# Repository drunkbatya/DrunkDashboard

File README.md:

# DrunkDashboard

## About

An STM32-based automotive dashboard with a sunlight-readable pixel display, running a port of the [Flipper Zero OS](https://github.com/flipperdevices/flipperzero-firmware).

### Front
<picture>
    
</picture>

### Back
<picture>
    
</picture>

### Specs
- MCU: stm32u585
- Display: Winstar WG24064, RA6963-based
- Canbus
- 8xADC
- 8x12v logic level inputs

## Hardware
Kicad source and production files lives in [hardware](./hardware) directory.

## Building
### Tools
arm-none-eabi-gcc toolchain needs to be installed, also make, python3 and icon converter deps:
```bash
python3 -m pip install -r scripts/requirements.txt 
```
openocd is required for flashing and arm-none-eabi-gdb for debugging

### Build
```bash
git submodule update --init --recursive
make
```

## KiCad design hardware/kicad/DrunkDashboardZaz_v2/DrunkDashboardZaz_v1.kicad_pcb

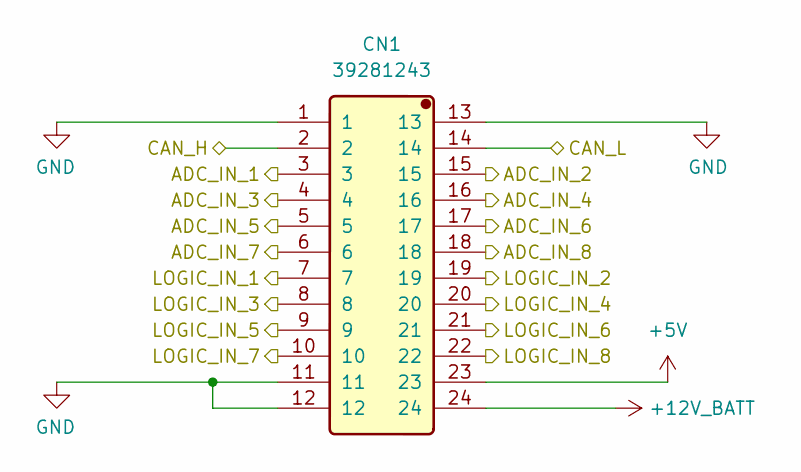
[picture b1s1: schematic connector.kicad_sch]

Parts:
CN1: 39281243; Manufacturer Part 39281243; LCSC C114088

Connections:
+5V: CN1.23; also elsewhere on the board
+12V_BATT: CN1.24; also elsewhere on the board
/ADC/ADC_IN_1: CN1.3; also elsewhere on the board
/ADC/ADC_IN_2: CN1.15; also elsewhere on the board
/ADC/ADC_IN_3: CN1.4; also elsewhere on the board
/ADC/ADC_IN_4: CN1.16; also elsewhere on the board
/ADC/ADC_IN_5: CN1.5; also elsewhere on the board
/ADC/ADC_IN_6: CN1.17; also elsewhere on the board
/ADC/ADC_IN_7: CN1.6; also elsewhere on the board
/ADC/ADC_IN_8: CN1.18; also elsewhere on the board
/CAN/CAN_H: CN1.2; also elsewhere on the board
/CAN/CAN_L: CN1.14; also elsewhere on the board
/Connector/LOGIC_IN_1: CN1.7; also elsewhere on the board
/Connector/LOGIC_IN_2: CN1.19; also elsewhere on the board
/Connector/LOGIC_IN_3: CN1.8; also elsewhere on the board
/Connector/LOGIC_IN_4: CN1.20; also elsewhere on the board
/Connector/LOGIC_IN_5: CN1.9; also elsewhere on the board
/Connector/LOGIC_IN_6: CN1.21; also elsewhere on the board
/Connector/LOGIC_IN_7: CN1.10; also elsewhere on the board
/Connector/LOGIC_IN_8: CN1.22; also elsewhere on the board
GND: CN1.1, CN1.11, CN1.12, CN1.13; also elsewhere on the board

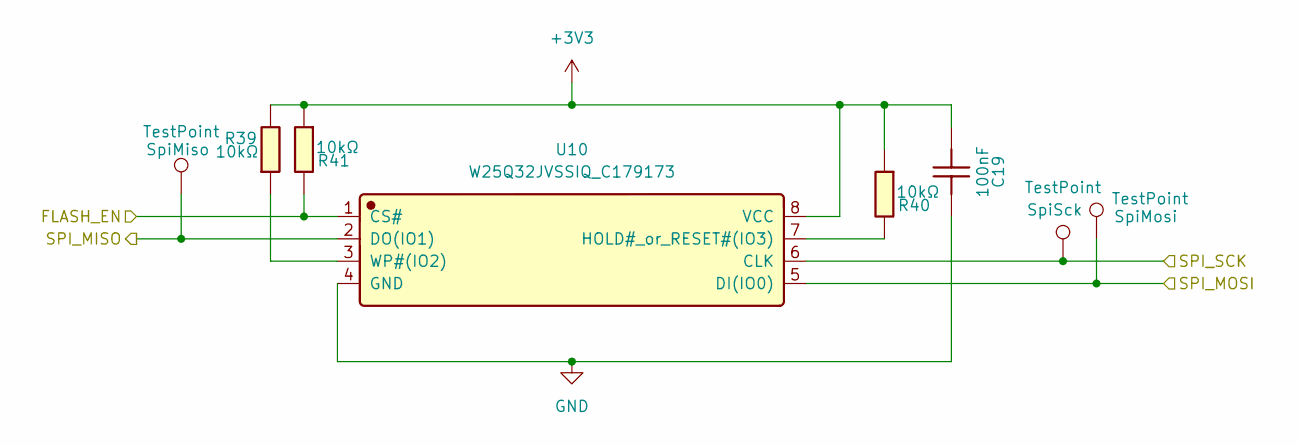
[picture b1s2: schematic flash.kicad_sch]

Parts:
C19: CL10B104KB8NNNC; C_0603_1608Metric; Manufacturer Part CL10B104KB8NNNC; LCSC C1591
R39, R40, R41: RT0603BRD0710KL; R_0603_1608Metric; Manufacturer Part RT0603BRD0710KL; LCSC C95204
SpiMiso_1: SpiMiso; TestPoint_Pad_D1.5mm
SpiMosi_1: SpiMosi; TestPoint_Pad_D1.5mm
SpiSck_1: SpiSck; TestPoint_Pad_D1.5mm
U10: W25Q32JVSSIQ_C179173; Manufacturer Part W25Q32JVSSIQ; LCSC C179173

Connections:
+3V3: C19.1, R39.2, R40.1, R41.1, U10.8 (VCC); also elsewhere on the board
/Flash/FLASH_EN: R41.2, U10.1 (CS#); also elsewhere on the board
/Flash/SPI_MISO: SpiMiso_1.1 (1_1), U10.2 (DO(IO1)); also elsewhere on the board
/Flash/SPI_MOSI: SpiMosi_1.1 (1_1), U10.5 (DI(IO0)); also elsewhere on the board
/Flash/SPI_SCK: SpiSck_1.1 (1_1), U10.6 (CLK); also elsewhere on the board
GND: C19.2, U10.4 (GND); also elsewhere on the board
unnamed: R40.2, U10.7 (HOLD#_or_RESET#(IO3))
unnamed: R39.1, U10.3 (WP#(IO2))

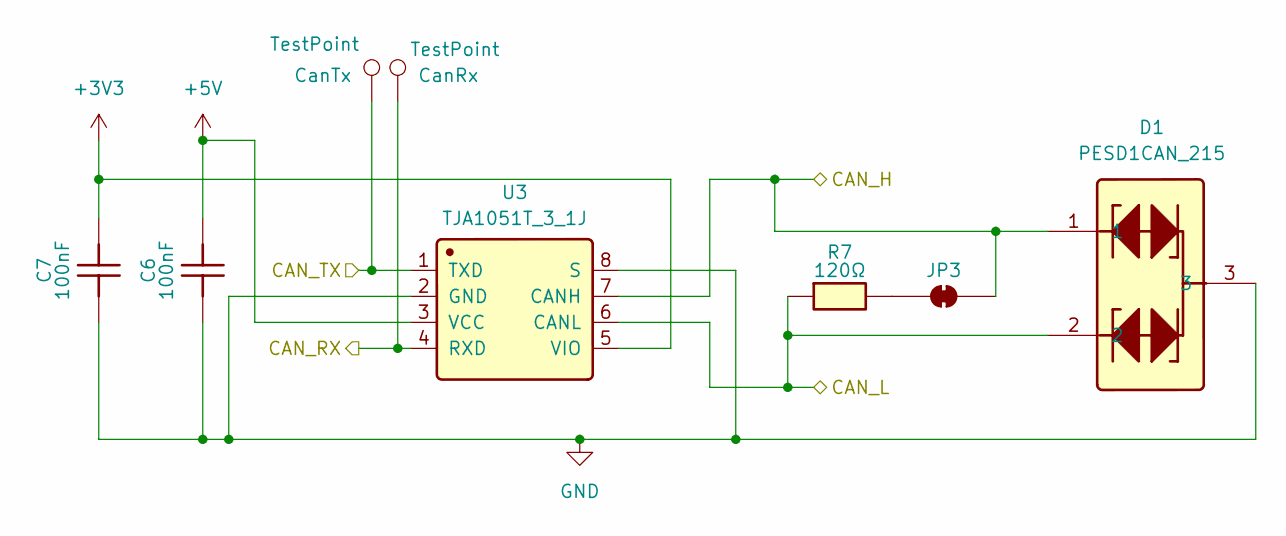
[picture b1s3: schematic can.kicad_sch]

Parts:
C6, C7: CL10B104KB8NNNC; C_0603_1608Metric; Manufacturer Part CL10B104KB8NNNC; LCSC C1591
CanRx_1: CanRx; TestPoint_Pad_D1.5mm
CanTx_1: CanTx; TestPoint_Pad_D1.5mm
D1: PESD1CAN_215; Manufacturer Part PESD1CAN,215; LCSC C15771
JP3: SolderJumper_2_Bridged; SolderJumper-2_P1.3mm_Bridged_RoundedPad1.0x1.5mm
R7: FRC0603F1200TS; R_0603_1608Metric; Manufacturer Part FRC0603F1200TS; LCSC C2906988
U3: TJA1051T_3_1J; Manufacturer Part TJA1051T/3/1J; LCSC C38695

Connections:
+3V3: C7.2, U3.5 (VIO); also elsewhere on the board
+5V: C6.2, U3.3 (VCC); also elsewhere on the board
/CAN/CAN_H: D1.1, JP3.2 (B), U3.7 (CANH); also elsewhere on the board
/CAN/CAN_L: D1.2, R7.1, U3.6 (CANL); also elsewhere on the board
/CAN/CAN_RX: CanRx_1.1 (1_1), U3.4 (RXD); also elsewhere on the board
/CAN/CAN_TX: CanTx_1.1 (1_1), U3.1 (TXD); also elsewhere on the board
GND: C6.1, C7.1, D1.3, U3.2 (GND), U3.8 (S); also elsewhere on the board
unnamed: JP3.1 (A), R7.2

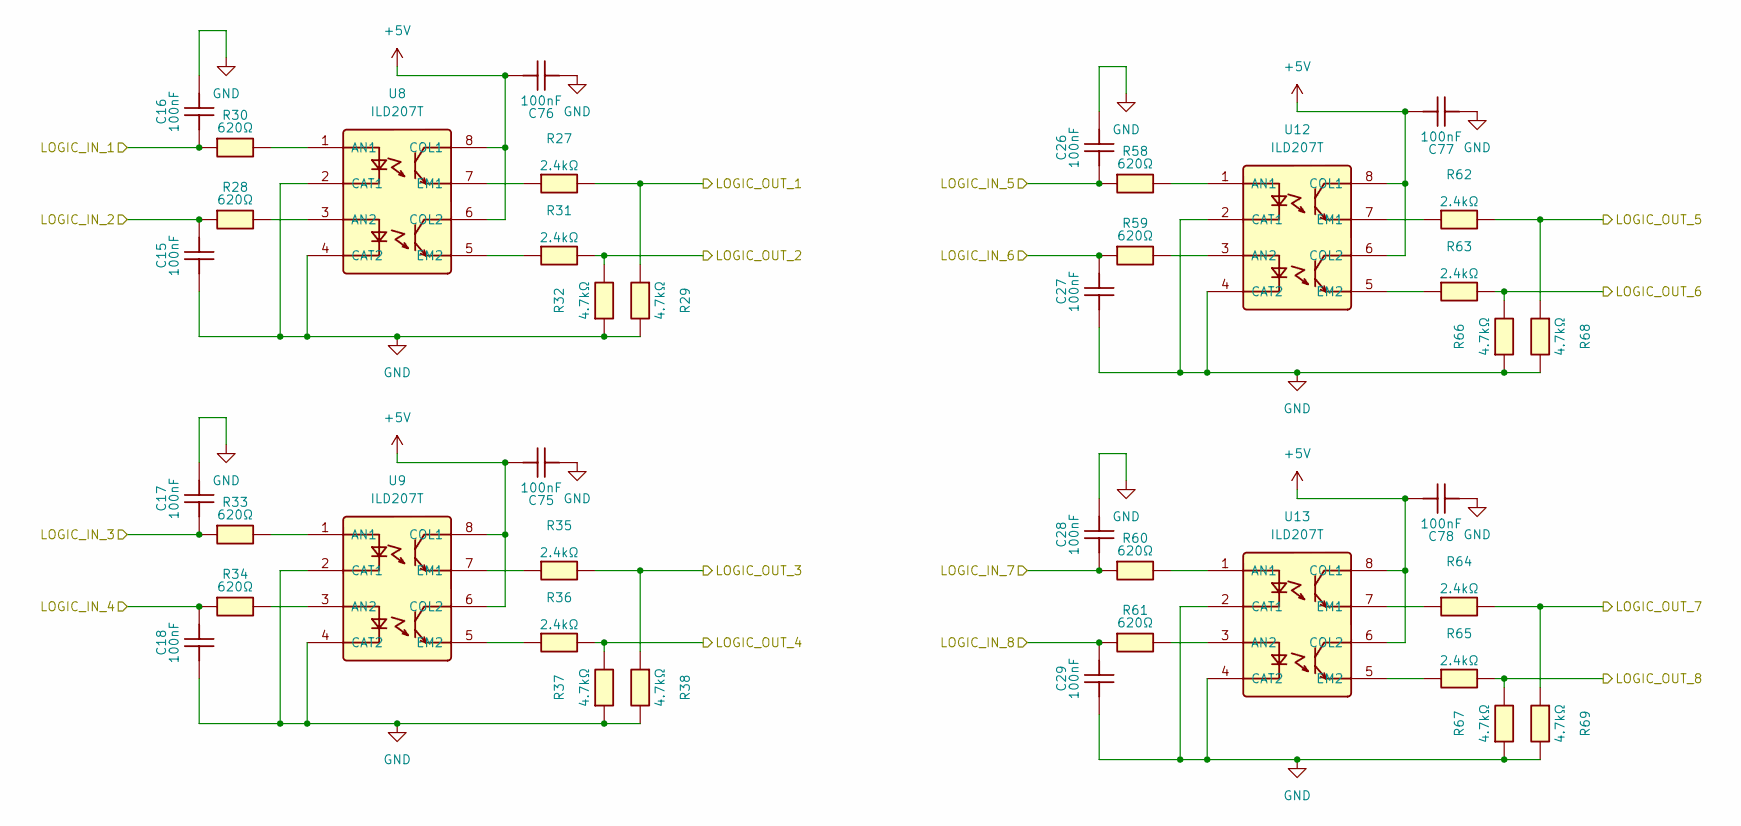
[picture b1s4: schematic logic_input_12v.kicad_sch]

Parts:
C15, C16, C17, C18, C26, C27, C28, C29, C75, C76, C77, C78: CL10B104KB8NNNC; C_0603_1608Metric; Manufacturer Part CL10B104KB8NNNC; LCSC C1591
R27, R31, R35, R36, R62, R63, R64, R65: FRC0603F2401TS; R_0603_1608Metric; Manufacturer Part FRC0603F2401TS; LCSC C2907007
R28, R30, R33, R34, R58, R59, R60, R61: FRC0603F6200TS; R_0603_1608Metric; Manufacturer Part FRC0603F6200TS; LCSC C2907058
R29, R32, R37, R38, R66, R67, R68, R69: FRC0603F4701TS; R_0603_1608Metric; Manufacturer Part FRC0603F4701TS; LCSC C2907034
U8, U9, U12, U13: ILD207T; Manufacturer Part ILD207T; LCSC C71049

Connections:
+5V: C75.2, C76.2, C77.2, C78.2, U8.6 (COL2), U8.8 (COL1), U9.6 (COL2), U9.8 (COL1), U12.6 (COL2), U12.8 (COL1), U13.6 (COL2), U13.8 (COL1); also elsewhere on the board
/Connector/LOGIC_IN_1: C16.1, R30.1; also elsewhere on the board
/Connector/LOGIC_IN_2: C15.2, R28.1; also elsewhere on the board
/Connector/LOGIC_IN_3: C17.1, R33.1; also elsewhere on the board
/Connector/LOGIC_IN_4: C18.2, R34.1; also elsewhere on the board
/Connector/LOGIC_IN_5: C26.1, R58.1; also elsewhere on the board
/Connector/LOGIC_IN_6: C27.2, R59.1; also elsewhere on the board
/Connector/LOGIC_IN_7: C28.1, R60.1; also elsewhere on the board
/Connector/LOGIC_IN_8: C29.2, R61.1; also elsewhere on the board
/MCU/TIM1_CH1: R63.2, R66.2; also elsewhere on the board
/MCU/TIM1_CH2: R62.2, R68.1; also elsewhere on the board
/MCU/TIM3_CH1: R36.2, R37.2; also elsewhere on the board
/MCU/TIM3_CH2: R35.2, R38.1; also elsewhere on the board
/MCU/TIM4_CH1: R31.2, R32.2; also elsewhere on the board
/MCU/TIM4_CH2: R27.2, R29.1; also elsewhere on the board
/MCU/TIM15_CH1: R65.2, R67.2; also elsewhere on the board
/MCU/TIM15_CH2: R64.2, R69.1; also elsewhere on the board
GND: C15.1, C16.2, C17.2, C18.1, C26.2, C27.1, C28.2, C29.1, C75.1, C76.1, C77.1, C78.1, R29.2, R32.1, R37.1, R38.2, R66.1, R67.1, R68.2, R69.2, U8.2 (CAT1), U8.4 (CAT2), U9.2 (CAT1), U9.4 (CAT2), U12.2 (CAT1), U12.4 (CAT2), U13.2 (CAT1), U13.4 (CAT2); also elsewhere on the board
unnamed: R30.2, U8.1 (AN1)
unnamed: R28.2, U8.3 (AN2)
unnamed: R27.1, U8.7 (EM1)
unnamed: R31.1, U8.5 (EM2)
unnamed: R33.2, U9.1 (AN1)
unnamed: R34.2, U9.3 (AN2)
unnamed: R35.1, U9.7 (EM1)
unnamed: R36.1, U9.5 (EM2)
unnamed: R58.2, U12.1 (AN1)
unnamed: R59.2, U12.3 (AN2)
unnamed: R62.1, U12.7 (EM1)
unnamed: R63.1, U12.5 (EM2)
unnamed: R60.2, U13.1 (AN1)
unnamed: R61.2, U13.3 (AN2)
unnamed: R64.1, U13.7 (EM1)
unnamed: R65.1, U13.5 (EM2)

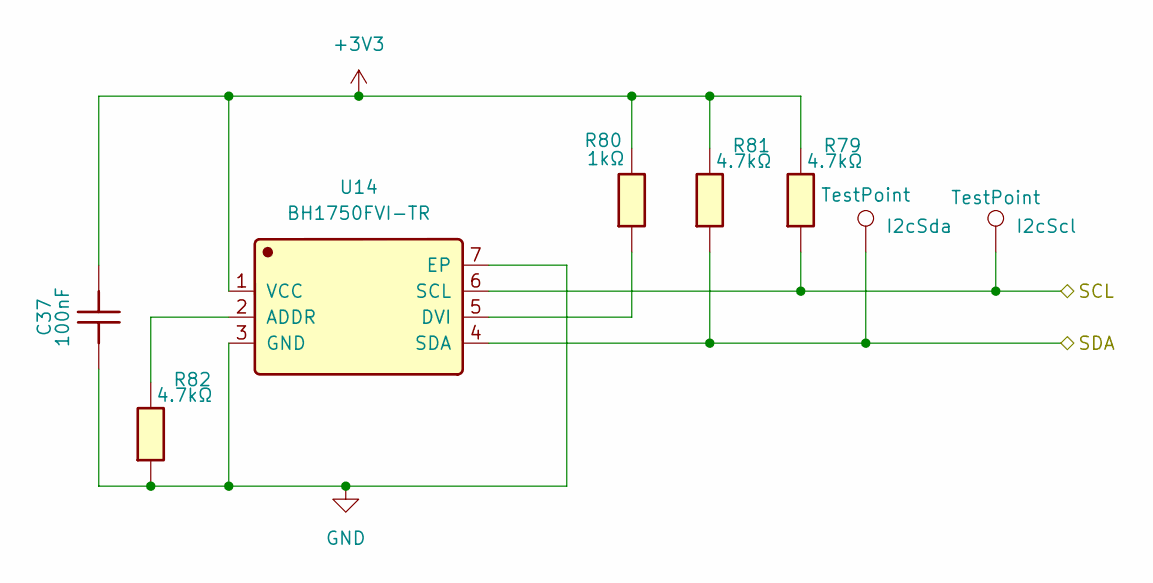
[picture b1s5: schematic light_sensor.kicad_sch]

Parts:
C37: CL10B104KB8NNNC; C_0603_1608Metric; Manufacturer Part CL10B104KB8NNNC; LCSC C1591
I2cScl_1: I2cScl; TestPoint_Pad_D1.5mm
I2cSda_1: I2cSda; TestPoint_Pad_D1.5mm
R79, R81, R82: FRC0603F4701TS; R_0603_1608Metric; Manufacturer Part FRC0603F4701TS; LCSC C2907034
R80: FRC0603F1001TS; R_0603_1608Metric; Manufacturer Part FRC0603F1001TS; LCSC C2907002
U14: BH1750FVI-TR; Manufacturer Part BH1750FVI-TR; LCSC C78960

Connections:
+3V3: C37.2, R79.2, R80.2, R81.2, U14.1 (VCC); also elsewhere on the board
/LightSensor/SCL: I2cScl_1.1 (1_1), R79.1, U14.6 (SCL); also elsewhere on the board
/LightSensor/SDA: I2cSda_1.1 (1_1), R81.1, U14.4 (SDA); also elsewhere on the board
GND: C37.1, R82.1, U14.3 (GND), U14.7 (EP); also elsewhere on the board
unnamed: R82.2, U14.2 (ADDR)
unnamed: R80.1, U14.5 (DVI)

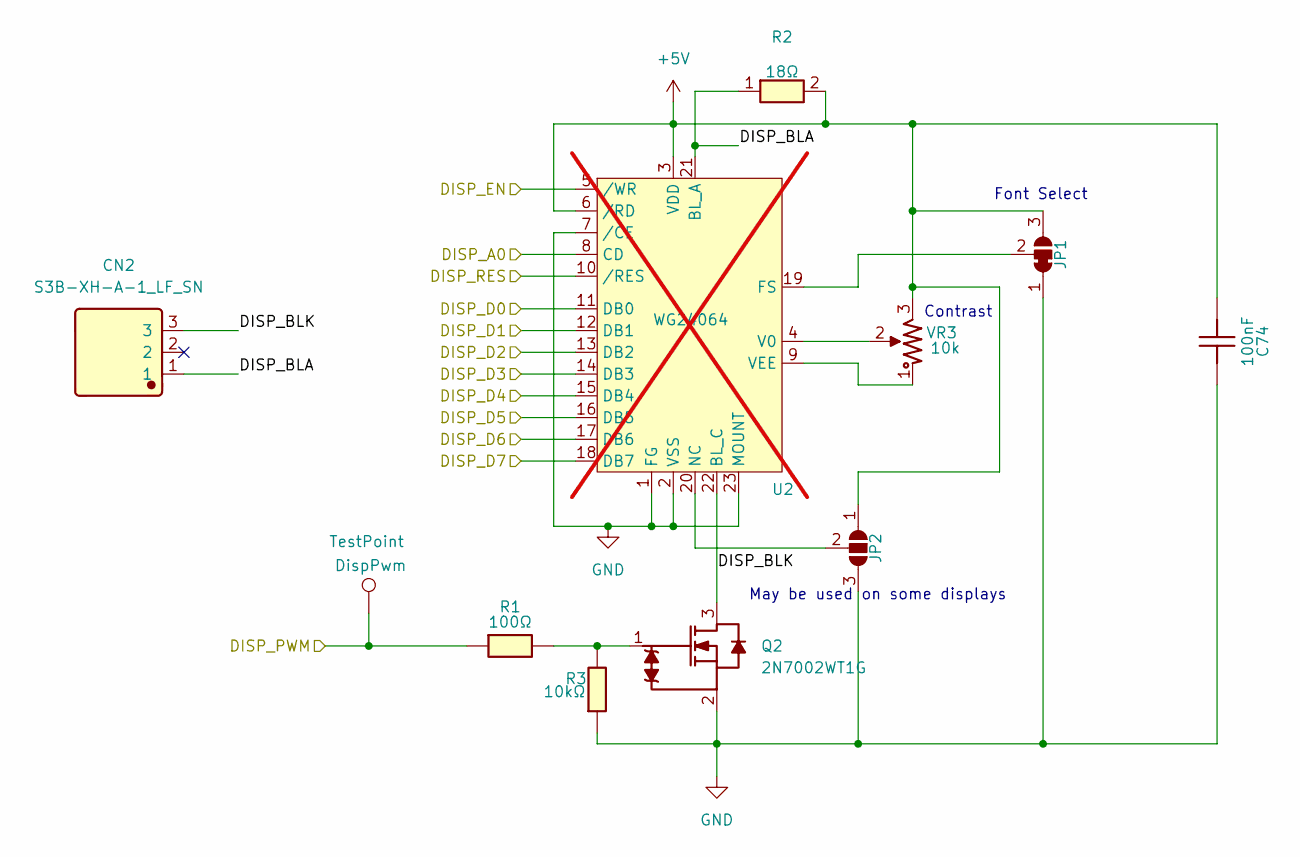
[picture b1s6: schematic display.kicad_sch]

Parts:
C74: CL10B104KB8NNNC; C_0603_1608Metric; Manufacturer Part CL10B104KB8NNNC; LCSC C1591
CN2: S3B-XH-A-1_LF_SN; Manufacturer Part S3B-XH-A-1(LF)(SN); LCSC C163036
DispPwm1: DispPwm; TestPoint_Pad_D1.5mm
JP1: SolderJumper_3_Bridged12; SolderJumper-3_P1.3mm_Bridged2Bar12_RoundedPad1.0x1.5mm
JP2: SolderJumper_3_Open; SolderJumper-3_P1.3mm_Open_RoundedPad1.0x1.5mm
Q2: 2N7002WT1G; SOT-323_SC-70; Manufacturer Part 2N7002WT1G; LCSC C232391
R1: PTFR0603B100RN9; R_0603_1608Metric; Manufacturer Part PTFR0603B100RN9; LCSC C394538
R2: RK73B2ETTD180J; R_1210_3225Metric; Manufacturer Part RK73B2ETTD180J; LCSC C830159
R3: RT0603BRD0710KL; R_0603_1608Metric; Manufacturer Part RT0603BRD0710KL; LCSC C95204
U2: WG24064; not fitted
VR3: 3362P-1-103LF_C48997950; Manufacturer Part 3362P-1-103LF; LCSC C48997950

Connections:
+5V: C74.2, JP1.3 (B), JP2.1 (A), R2.2, U2.3 (VDD), U2.6 (/RD), VR3.3; also elsewhere on the board
/Display/DISP_A0: U2.8 (CD); also elsewhere on the board
/Display/DISP_BLA: CN2.1, R2.1, U2.21 (BL_A)
/Display/DISP_BLK: CN2.3, Q2.3 (D), U2.22 (BL_C)
/Display/DISP_D0: U2.11 (DB0); also elsewhere on the board
/Display/DISP_D1: U2.12 (DB1); also elsewhere on the board
/Display/DISP_D2: U2.13 (DB2); also elsewhere on the board
/Display/DISP_D3: U2.14 (DB3); also elsewhere on the board
/Display/DISP_D4: U2.15 (DB4); also elsewhere on the board
/Display/DISP_D5: U2.16 (DB5); also elsewhere on the board
/Display/DISP_D6: U2.17 (DB6); also elsewhere on the board
/Display/DISP_D7: U2.18 (DB7); also elsewhere on the board
/Display/DISP_EN: U2.5 (/WR); also elsewhere on the board
/Display/DISP_PWM: DispPwm1.1 (1_1), R1.1; also elsewhere on the board
/Display/DISP_RES: U2.10 (/RES); also elsewhere on the board
GND: C74.1, JP1.1 (A), JP2.3 (B), Q2.2 (S), R3.1, U2.1 (FG), U2.2 (VSS), U2.7 (/CE), U2.23 (MOUNT); also elsewhere on the board
unnamed: JP1.2 (C), U2.19 (FS)
unnamed: JP2.2 (C), U2.20 (NC)
unnamed: Q2.1 (G), R1.2, R3.2
unnamed: U2.4 (V0), VR3.2
unnamed: U2.9 (VEE), VR3.1

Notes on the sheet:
May be used on some displays
Font Select
Contrast

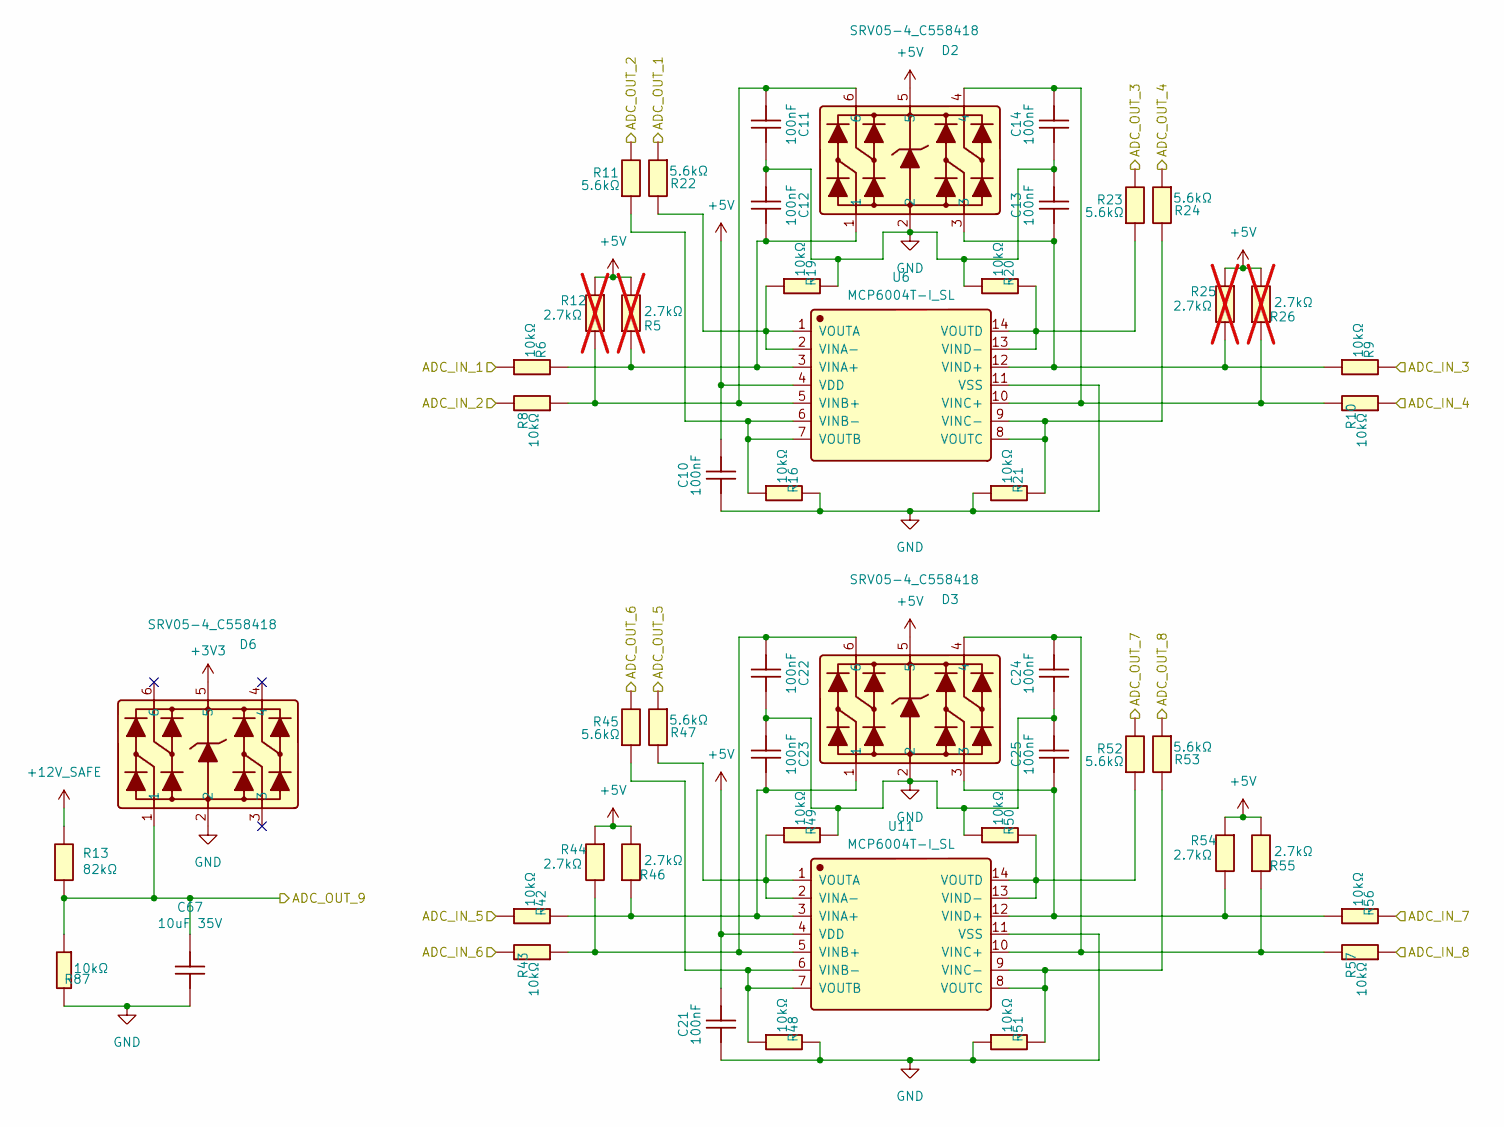
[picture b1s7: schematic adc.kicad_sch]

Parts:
C10, C11, C12, C13, C14, C21, C22, C23, C24, C25: CL10B104KB8NNNC; C_0603_1608Metric; Manufacturer Part CL10B104KB8NNNC; LCSC C1591
C67: GRM21BC8YA106KE11L; C_0805_2012Metric; Manufacturer Part GRM21BC8YA106KE11L; LCSC C469541
D2, D3, D6: SRV05-4_C558418; Manufacturer Part SRV05-4; LCSC C558418
R5, R12, R25, R26: FRC0603F2701TS; R_0603_1608Metric; Manufacturer Part FRC0603F2701TS; LCSC C2907008; not fitted
R6, R8, R9, R10, R16, R19, R20, R21, R42, R43, R48, R49, R50, R51, R56, R57, R87: RT0603BRD0710KL; R_0603_1608Metric; Manufacturer Part RT0603BRD0710KL; LCSC C95204
R11, R22, R23, R24, R45, R47, R52, R53: FRC0603F5601TS; R_0603_1608Metric; Manufacturer Part FRC0603F5601TS; LCSC C2907046
R13: FRC0603F8202TS; R_0603_1608Metric; Manufacturer Part FRC0603F8202TS; LCSC C2907072
R44, R46, R54, R55: FRC0603F2701TS; R_0603_1608Metric; Manufacturer Part FRC0603F2701TS; LCSC C2907008
U6, U11: MCP6004T-I_SL; Manufacturer Part MCP6004T-I/SL; LCSC C7378

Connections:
+3V3: D6.5; also elsewhere on the board
+5V: C10.2, C21.2, D2.5, D3.5, R5.2, R12.1, R25.1, R26.2, R44.1, R46.2, R54.1, R55.2, U6.4 (VDD), U11.4 (VDD); also elsewhere on the board
+12V_SAFE: R13.2; also elsewhere on the board
/ADC/ADC_IN_1: R6.1; also elsewhere on the board
/ADC/ADC_IN_2: R8.2; also elsewhere on the board
/ADC/ADC_IN_3: R9.2; also elsewhere on the board
/ADC/ADC_IN_4: R10.1; also elsewhere on the board
/ADC/ADC_IN_5: R42.1; also elsewhere on the board
/ADC/ADC_IN_6: R43.2; also elsewhere on the board
/ADC/ADC_IN_7: R56.2; also elsewhere on the board
/ADC/ADC_IN_8: R57.1; also elsewhere on the board
/ADC/ADC_OUT_1: R22.1; also elsewhere on the board
/ADC/ADC_OUT_2: R11.2; also elsewhere on the board
/ADC/ADC_OUT_3: R23.2; also elsewhere on the board
/ADC/ADC_OUT_4: R24.1; also elsewhere on the board
/ADC/ADC_OUT_5: R47.1; also elsewhere on the board
/ADC/ADC_OUT_6: R45.2; also elsewhere on the board
/ADC/ADC_OUT_7: R52.2; also elsewhere on the board
/ADC/ADC_OUT_8: R53.1; also elsewhere on the board
/ADC/ADC_OUT_9: C67.2, D6.1, R13.1, R87.1; also elsewhere on the board
GND: C10.1, C11.2, C12.1, C13.2, C14.1, C21.1, C22.2, C23.1, C24.1, C25.2, C67.1, D2.2, D3.2, D6.2, R16.2, R19.2, R20.1, R21.1, R48.2, R49.2, R50.1, R51.1, R87.2, U6.11 (VSS), U11.11 (VSS); also elsewhere on the board
unnamed: C12.2, D2.1, R5.1, R6.2, U6.3 (VINA+)
unnamed: R19.1, R22.2, U6.1 (VOUTA), U6.2 (VINA-)
unnamed: C11.1, D2.6, R8.1, R12.2, U6.5 (VINB+)
unnamed: R11.1, R16.1, U6.6 (VINB-), U6.7 (VOUTB)
unnamed: C14.2, D2.4, R10.2, R26.1, U6.10 (VINC+)
unnamed: R21.2, R24.2, U6.8 (VOUTC), U6.9 (VINC-)
unnamed: C13.1, D2.3, R9.1, R25.2, U6.12 (VIND+)
unnamed: R20.2, R23.1, U6.13 (VIND-), U6.14 (VOUTD)
unnamed: C23.2, D3.1, R42.2, R46.1, U11.3 (VINA+)
unnamed: R47.2, R49.1, U11.1 (VOUTA), U11.2 (VINA-)
unnamed: C22.1, D3.6, R43.1, R44.2, U11.5 (VINB+)
unnamed: R45.1, R48.1, U11.6 (VINB-), U11.7 (VOUTB)
unnamed: C24.2, D3.4, R55.1, R57.2, U11.10 (VINC+)
unnamed: R51.2, R53.2, U11.8 (VOUTC), U11.9 (VINC-)
unnamed: C25.1, D3.3, R54.2, R56.1, U11.12 (VIND+)
unnamed: R50.2, R52.1, U11.13 (VIND-), U11.14 (VOUTD)

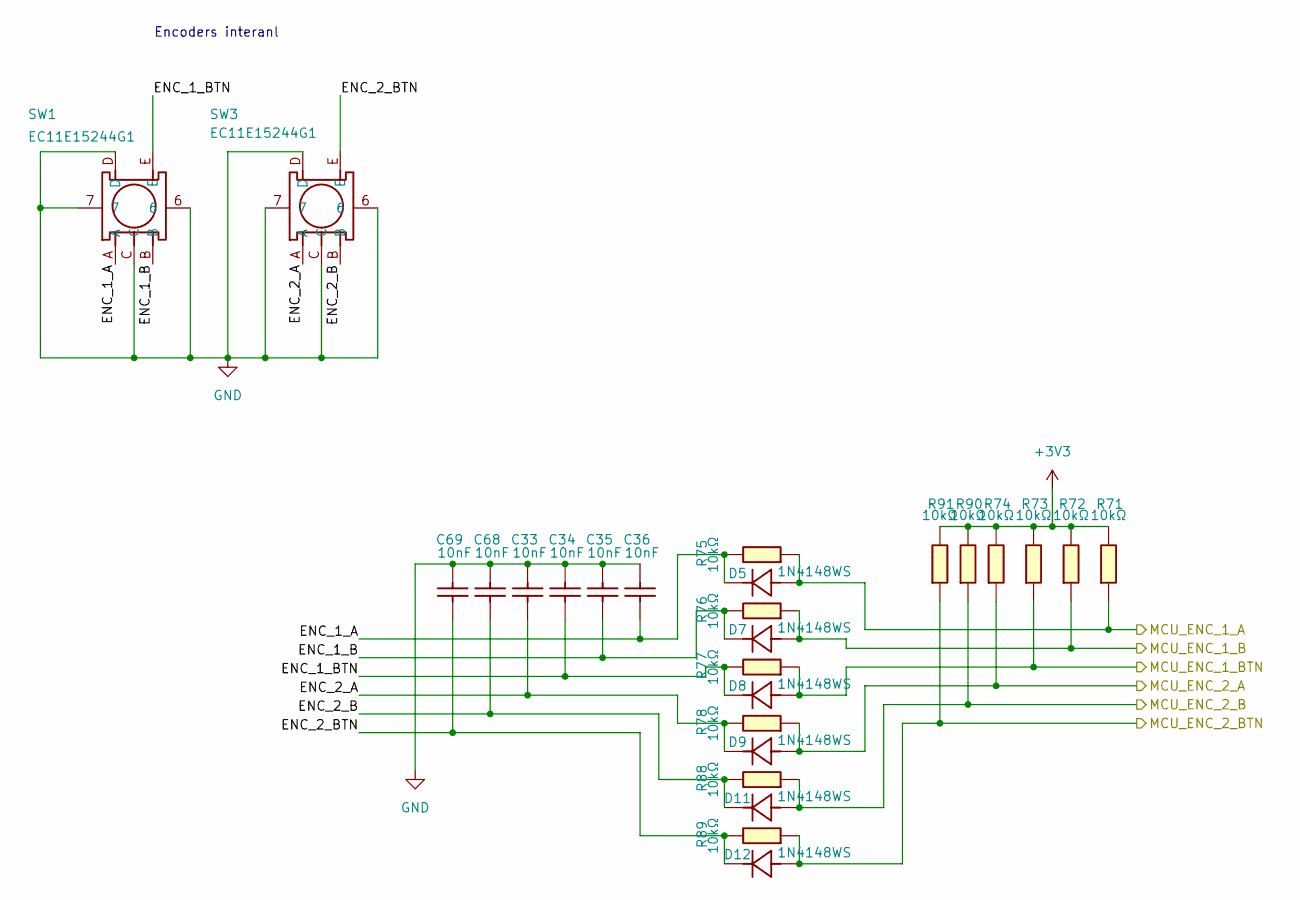
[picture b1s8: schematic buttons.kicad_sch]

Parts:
C33, C34, C35, C36, C68, C69: CC0603KRX7R0BB103; C_0603_1608Metric; Manufacturer Part CC0603KRX7R0BB103; LCSC C107059
D5, D7, D8, D9, D11, D12: 1N4148WS_C917117; Manufacturer Part 1N4148WS; LCSC C917117
R71, R72, R73, R74, R75, R76, R77, R78, R88, R89, R90, R91: RT0603BRD0710KL; R_0603_1608Metric; Manufacturer Part RT0603BRD0710KL; LCSC C95204
SW1, SW3: EC11E15244G1; Manufacturer Part EC11E15244G1; LCSC C370970

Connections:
+3V3: R71.2, R72.2, R73.2, R74.2, R90.2, R91.2; also elsewhere on the board
/Buttons/ENC_1_A: C36.2, D5.1 (C), R75.2, SW1.A
/Buttons/ENC_1_B: C35.2, D7.1 (C), R76.2, SW1.B
/Buttons/ENC_1_BTN: C34.2, D8.1 (C), R77.2, SW1.E
/Buttons/ENC_2_A: C33.2, D9.1 (C), R78.2, SW3.A
/Buttons/ENC_2_B: C68.2, D11.1 (C), R88.2, SW3.B
/Buttons/ENC_2_BTN: C69.2, D12.1 (C), R89.2, SW3.E
/Buttons/MCU_ENC_1_A: D5.2 (A), R71.1, R75.1; also elsewhere on the board
/Buttons/MCU_ENC_1_B: D7.2 (A), R72.1, R76.1; also elsewhere on the board
/Buttons/MCU_ENC_1_BTN: D8.2 (A), R73.1, R77.1; also elsewhere on the board
/Buttons/MCU_ENC_2_A: D9.2 (A), R74.1, R78.1; also elsewhere on the board
/Buttons/MCU_ENC_2_B: D11.2 (A), R88.1, R90.1; also elsewhere on the board
/Buttons/MCU_ENC_2_BTN: D12.2 (A), R89.1, R91.1; also elsewhere on the board
GND: C33.1, C34.1, C35.1, C36.1, C68.1, C69.1, SW1.6, SW1.7, SW1.C, SW1.D, SW3.6, SW3.7, SW3.C, SW3.D; also elsewhere on the board

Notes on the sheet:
Encoders interanl

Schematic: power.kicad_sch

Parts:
3v3_1: 3v3; TestPoint_Pad_D1.5mm
5v1: 5v; TestPoint_Pad_D1.5mm
12v_1: 12v; TestPoint_Pad_D1.5mm
C9: 25TQC22MYFB; Manufacturer Part 25TQC22MYFB; LCSC C3018703
C38: EEFCX0J101R; Manufacturer Part EEFCX0J101R; LCSC C189619
C39, C40, C41, C42: GCM21BR71A106KE22L; Manufacturer Part GCM21BR71A106KE22L; LCSC C126586
C43: CL10A475KO8NNNC; C_0603_1608Metric; Manufacturer Part CL10A475KO8NNNC; LCSC C19666
C44, C45, C46: CL10B104KB8NNNC; C_0603_1608Metric; Manufacturer Part CL10B104KB8NNNC; LCSC C1591
C47: CC0603KRX7R0BB104; C_0603_1608Metric; Manufacturer Part CC0603KRX7R0BB104; LCSC C113803
C49, C52, C53, C54, C55, C56: GRM21BC8YA106KE11L; C_0805_2012Metric; Manufacturer Part GRM21BC8YA106KE11L; LCSC C469541
C50, C57: CC0603KRX7R0BB221; C_0603_1608Metric; Manufacturer Part CC0603KRX7R0BB221; LCSC C107061
C51: CC0603KRX7R9BB122; C_0603_1608Metric; Manufacturer Part CC0603KRX7R9BB122; LCSC C107073
D10: MMBZ5242BLT3G; Manufacturer Part MMBZ5242BLT3G; LCSC C896784
GND1: GND; TestPoint_Pad_2.0x2.0mm
L3: SRN6045TA-3R3Y; Manufacturer Part SRN6045TA-3R3Y; LCSC C3221229
Q3: DMP3013SFV-7_ES; Manufacturer Part DMP3013SFV-7(ES); LCSC C42412325
R83, R86: RC0603FR-0712KL; R_0603_1608Metric; Manufacturer Part RC0603FR-0712KL; LCSC C114659
R84: FRC0603F2002TS; R_0603_1608Metric; Manufacturer Part FRC0603F2002TS; LCSC C2907011
R85: FRC0603F2201TS; R_0603_1608Metric; Manufacturer Part FRC0603F2201TS; LCSC C2907005
U4: AMS1117-3_3; Manufacturer Part AMS1117-3.3; LCSC C6186
U5: AP64501SP-13; SOIC-8-1EP_3.9x4.9mm_P1.27mm_EP2.95x4.9mm_Mask2.71x3.4mm_Th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; Manufacturer Part AP64501SP-13; LCSC C2071517
U16: CRCW060310R0FKEAHP; R_0603_1608Metric; Manufacturer Part CRCW060310R0FKEAHP; LCSC C313648

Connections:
+3V3: 3v3_1.1 (1_1), C9.1, C43.2, U4.2 (VOUT), U4.4 (VOUT); also elsewhere on the board
+5V: 5v1.1 (1_1), C38.1, C39.2, C40.2, C41.2, C42.2, C50.1, L3.2, R86.2, U4.3 (VIN); also elsewhere on the board
+12V_BATT: C47.2, Q3.5 (D); also elsewhere on the board
+12V_SAFE: 12v_1.1 (1_1), C44.1, C49.2, C52.2, C53.2, C54.2, C55.2, C56.2, D10.3, Q3.1 (S), Q3.2 (S), Q3.3 (S), U5.2 (VIN), U5.3 (EN); also elsewhere on the board
GND: C9.2, C38.2, C39.1, C40.1, C41.1, C42.1, C43.1, C46.1, C47.1, C49.1, C51.2, C52.1, C53.1, C54.1, C55.1, C56.1, C57.2, GND1.1 (1_1), R83.2, R85.2, U4.1 (GND), U5.7 (GND), U5.9 (EP); also elsewhere on the board
unnamed: C45.2, U16.1
unnamed: C51.1, R84.2
unnamed: C44.2, D10.1, Q3.4 (G), R83.1
unnamed: C45.1, U5.1 (BST)
unnamed: C57.1, R84.1, U5.6 (COMP)
unnamed: C50.2, R85.1, R86.1, U5.5 (FB)
unnamed: C46.2, U5.4 (SS)
unnamed: L3.1, U5.8 (SW), U16.2

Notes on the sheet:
Ideal diode to prevent reverse polarity at the input
5v @ 3A PSU
3.3v Supply

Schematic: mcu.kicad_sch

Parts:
B1: BS-02-A1AJ010; Manufacturer Part BS-02-A1AJ010; LCSC C5239862
C1, C2, C3, C4: CL10C180JB8NNNC; C_0603_1608Metric; Manufacturer Part CL10C180JB8NNNC; LCSC C1647
C5: CC0603KRX7R0BB103; C_0603_1608Metric; Manufacturer Part CC0603KRX7R0BB103; LCSC C107059
C8, C30, C32, C48, C59, C62, C63, C64, C65, C66, C71, C72, C73: CL10B104KB8NNNC; C_0603_1608Metric; Manufacturer Part CL10B104KB8NNNC; LCSC C1591
C58, C60, C61: GRM188R61H225KE11D; C_0603_1608Metric; Manufacturer Part GRM188R61H225KE11D; LCSC C162273
C70: CC0603JRX7R7BB105; C_0603_1608Metric; Manufacturer Part CC0603JRX7R7BB105; LCSC C519560
D4: SS12_C18199177; Manufacturer Part SS12; LCSC C18199177
H1, H3: PZ254R-11-04P; Manufacturer Part PZ254R-11-04P; LCSC C492412
L1: LQM2HPN2R2MG0L; Manufacturer Part LQM2HPN2R2MG0L; LCSC C86092
L2: BLM18PG121SN1D_C14709; Manufacturer Part BLM18PG121SN1D; LCSC C14709
R4: RT0603BRD0710KL; R_0603_1608Metric; Manufacturer Part RT0603BRD0710KL; LCSC C95204
R70: PTFR0603B100RN9; R_0603_1608Metric; Manufacturer Part PTFR0603B100RN9; LCSC C394538
SW2: TS3643TP; Manufacturer Part TS3643TP; LCSC C398054
SW4: MINI_MSK12CO2; Manufacturer Part MINI MSK12CO2; LCSC C2681570
SpiCs2_1: SpiCs2; TestPoint_Pad_D1.5mm
U1: STM32U585VIT6Q; LQFP-100_14x14mm_P0.5mm; Manufacturer Part STM32U585VIT6Q; LCSC C5270986
U7: REF3333AIDBZR; Manufacturer Part REF3333AIDBZR; LCSC C130016
X1: X322525MOB4SI; Crystal_SMD_3225-4Pin_3.2x2.5mm; Manufacturer Part X322525MOB4SI; LCSC C9006
X2: Q13FC1350000400; Manufacturer Part Q13FC13500004; LCSC C32346

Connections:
+3V3: C62.2, C63.2, C64.2, C65.2, C66.2, C72.2, C73.2, D4.2 (A), L2.1, R4.2, U1.11 (VDD), U1.27 (VDD), U1.47 (VDDSMPS), U1.51 (VDD), U1.73 (VDDUSB), U1.75 (VDD), U1.100 (VDD); also elsewhere on the board
+5V: C8.2, H1.1, H3.1, U7.1 (IN); also elsewhere on the board
/ADC/ADC_OUT_1: U1.15 (PC0); also elsewhere on the board
/ADC/ADC_OUT_2: U1.16 (PC1); also elsewhere on the board
/ADC/ADC_OUT_3: U1.17 (PC2); also elsewhere on the board
/ADC/ADC_OUT_4: U1.18 (PC3); also elsewhere on the board
/ADC/ADC_OUT_5: U1.22 (PA0); also elsewhere on the board
/ADC/ADC_OUT_6: U1.23 (PA1); also elsewhere on the board
/ADC/ADC_OUT_7: U1.24 (PA2); also elsewhere on the board
/ADC/ADC_OUT_8: U1.25 (PA3); also elsewhere on the board
/ADC/ADC_OUT_9: U1.28 (PA4); also elsewhere on the board
/Buttons/MCU_ENC_1_A: U1.63 (PC6); also elsewhere on the board
/Buttons/MCU_ENC_1_B: U1.64 (PC7); also elsewhere on the board
/Buttons/MCU_ENC_1_BTN: U1.34 (PB2); also elsewhere on the board
/Buttons/MCU_ENC_2_A: U1.33 (PB1); also elsewhere on the board
/Buttons/MCU_ENC_2_B: U1.56 (PD9); also elsewhere on the board
/Buttons/MCU_ENC_2_BTN: U1.36 (PE8); also elsewhere on the board
/CAN/CAN_RX: U1.70 (PA11); also elsewhere on the board
/CAN/CAN_TX: U1.71 (PA12); also elsewhere on the board
/Display/DISP_A0: U1.80 (PC12); also elsewhere on the board
/Display/DISP_D0: U1.81 (PD0); also elsewhere on the board
/Display/DISP_D1: U1.82 (PD1); also elsewhere on the board
/Display/DISP_D2: U1.83 (PD2); also elsewhere on the board
/Display/DISP_D3: U1.84 (PD3); also elsewhere on the board
/Display/DISP_D4: U1.85 (PD4); also elsewhere on the board
/Display/DISP_D5: U1.86 (PD5); also elsewhere on the board
/Display/DISP_D6: U1.87 (PD6); also elsewhere on the board
/Display/DISP_D7: U1.88 (PD7); also elsewhere on the board
/Display/DISP_EN: U1.79 (PC11); also elsewhere on the board
/Display/DISP_PWM: U1.89 (PB3); also elsewhere on the board
/Display/DISP_RES: U1.78 (PC10); also elsewhere on the board
/Flash/FLASH_EN: U1.32 (PB0); also elsewhere on the board
/Flash/SPI_MISO: U1.30 (PA6); also elsewhere on the board
/Flash/SPI_MOSI: U1.31 (PA7); also elsewhere on the board
/Flash/SPI_SCK: U1.29 (PA5); also elsewhere on the board
/LightSensor/SCL: U1.95 (PB8); also elsewhere on the board
/LightSensor/SDA: U1.96 (PB9); also elsewhere on the board
/MCU/MCU_RESET: C5.1, R4.1, SW2.1, U1.14 (NRST)
/MCU/MCU_UART_RX: H3.3, U1.69 (PA10)
/MCU/MCU_UART_TX: H3.2, U1.68 (PA9)
/MCU/MCU_VBAT: C32.1, R70.2, SW4.3, U1.6 (VBAT)
/MCU/MCU_VDD11: C48.1, C58.1, C59.2, C60.2, L1.1, U1.49 (VDD11), U1.98 (VDD11)
/MCU/MCU_VDDA: C30.2, C61.2, L2.2, U1.21 (VDDA)
/MCU/MCU_VREF: C70.2, C71.1, U1.20 (VREF+), U7.2 (OUT)
/MCU/SPI_CS_2: SpiCs2_1.1 (1_1), U1.35 (PE7)
/MCU/SWCLK: H1.3, U1.76 (PA14)
/MCU/SWDIO: H1.2, U1.72 (PA13)
/MCU/TIM1_CH1: U1.37 (PE9); also elsewhere on the board
/MCU/TIM1_CH2: U1.39 (PE11); also elsewhere on the board
/MCU/TIM3_CH1: U1.2 (PE3); also elsewhere on the board
/MCU/TIM3_CH2: U1.3 (PE4); also elsewhere on the board
/MCU/TIM4_CH1: U1.92 (PB6); also elsewhere on the board
/MCU/TIM4_CH2: U1.93 (PB7); also elsewhere on the board
/MCU/TIM15_CH1: U1.53 (PB14); also elsewhere on the board
/MCU/TIM15_CH2: U1.54 (PB15); also elsewhere on the board
GND: B1.1, C1.2, C2.2, C3.1, C4.1, C5.2, C8.1, C30.1, C32.2, C48.2, C58.2, C59.1, C60.1, C61.1, C62.1, C63.1, C64.1, C65.1, C66.1, C70.1, C71.2, C72.1, C73.1, H1.4, H3.4, SW2.2, SW4.4, SW4.5, U1.10 (VSS), U1.19 (VSSA), U1.26 (VSS), U1.48 (VSSSMPS), U1.50 (VSS), U1.74 (VSS), U1.94 (PH3-BOOT0), U1.99 (VSS), U7.3 (GND), X1.2 (GND), X1.4 (GND); also elsewhere on the board
unnamed: B1.2, R70.1
unnamed: D4.1 (K), SW4.2
unnamed: C4.2, U1.8 (PC14-OSC32_IN), X2.1
unnamed: C3.2, U1.9 (PC15-OSC32_OUT), X2.2
unnamed: C2.1, U1.12 (PH0-OSC_IN), X1.1 (OSC1)
unnamed: C1.1, U1.13 (PH1-OSC_OUT), X1.3 (OSC2)
unnamed: L1.2, U1.46 (VLXSMPS)

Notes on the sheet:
SWD
UART
